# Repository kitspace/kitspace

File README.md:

> ❗ Archived, new development here: [kitspace-v2](https://github.com/kitspace/kitspace-v2)

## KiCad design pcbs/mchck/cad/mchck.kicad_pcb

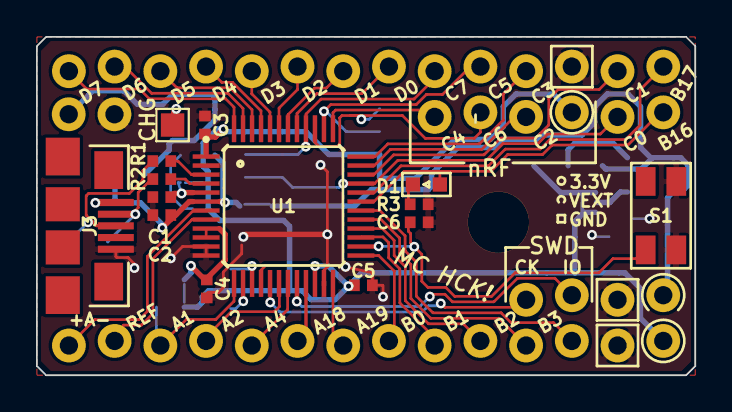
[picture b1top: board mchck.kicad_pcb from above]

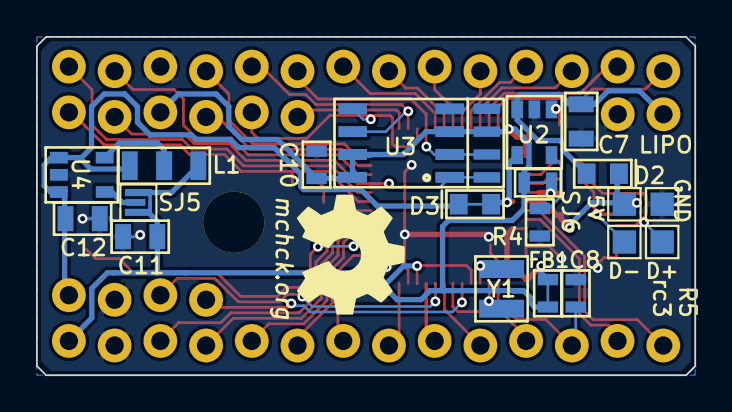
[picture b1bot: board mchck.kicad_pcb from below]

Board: 2 copper layers, 36.6 x 18.8 mm, 41 parts (26 on the bottom side), 51 nets.

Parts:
C1, C2: 2.2u; SMD-1005
C3, C4, C5, C6: 100n; SMD-1005
C7: 4.7u; SM0805
C8, C10: 100n; SM0603_Capa
C11, C12: 10u; SM0805
D1: LED; LED-0603
D2: CDBU0530; SOD-523F
D3: CDBU0530; SOD-523F-NC
FB1: FILTER; SM0603_NC
G1: OHW LOGO; OHW-LOGO-6mm
H1: MOUNTHOLE; mounthole_3mm
J3: MICRO_USB; SparkFun-USB-MICROB
L1: INDUCTOR_SELECT; SM0805-3WAY
P1: RIGHT_PINS; SparkFun-1X06_LOCK
P2: DEBUG; SparkFun-1X04_LOCK
P3: UPPER_PINS; SparkFun-1X14_LOCK
P4: LOWER_PINS; SparkFun-1X14_LOCK
P5: CHG; solderpad
P7: LIPO; SIL100-2
P9: 5V; solderpad
P10: GND; solderpad
P11: D-; solderpad
P12: D+; solderpad
R1, R2: 33; SMD-1005
R3: 1k; SMD-1005
R4: 20k; SM0603
S1: TAC_SWITCHSMD_EVQP2; TACT_4x3
SJ5: SOLDERJUMPERNO; solder-jumper
SJ6: SOLDERJUMPERNC; SM0603_NC
U1: MK20LF; LQFP48
U2: MCP73831-SOT; SOT23-5
U3: SPI_FLASH-X25XXSMD; SparkFun-SO08
U4: MULTIREG; SOT23-5
Y1: CRYSTAL32-SMD; SparkFun-CRYSTAL-32KHZ-SMD

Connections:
/MCU/+5V: C2.1, D2.C, D3.A, J3.1, P9.1, U1.6, U2.4
/MCU/PL1: P4.1, U1.7
/MCU/PL2: P4.2, U1.8
/MCU/PL3: C8.1, P4.3, U1.13
/MCU/PL4: P4.4, U1.18
/MCU/PL5: P4.5, U1.19
/MCU/PL6: P4.6, U1.21
/MCU/PL7: P4.7, U1.24
/MCU/PL8: P4.8, U1.25
/MCU/PL9: P4.9, U1.27
/MCU/PL10: P4.10, U1.28
/MCU/PL11: P4.11, U1.29
/MCU/PL12: P4.12, U1.30
/MCU/PR1: P1.1, U1.37
/MCU/PR2: P1.2, U1.39, U3.5
/MCU/PR3: P1.3, U1.35
/MCU/PR5: P1.5, U1.33, U3.1
/MCU/PR6: D1.1, P1.6, U1.31
/MCU/PU1: P3.1, U1.48
/MCU/PU2: P3.2, U1.47
/MCU/PU3: P3.3, U1.46
/MCU/PU4: P3.4, U1.45
/MCU/PU5: P3.5, U1.44
/MCU/PU6: P3.6, U1.43
/MCU/PU7: P3.7, U1.42
/MCU/PU8: P3.8, U1.41
/MCU/PU9: P3.9, U1.40, U3.2
/MCU/PU10: P3.10, U1.38, U3.6
/MCU/PU11: P3.11, U1.36
/MCU/PU13: P3.13, U1.34
/MCU/PU14: P3.14, U1.32
/MCU/SWD_CLK: P2.1, U1.17
/MCU/SWD_DIO: P2.2, U1.20
/MCU/USB_DM: R2.2, U1.4
/MCU/USB_DP: R1.2, U1.3
/MCU/VREGUSB: C1.1, SJ6.1, U1.5
/USB/USB_D+: J3.3, P12.1, R1.1
/USB/USB_D-: J3.2, P11.1, R2.1
/power/VLIPO: C7.1, D2.A, P7.1, U2.3
/power/VRAW: C12.1, D3.C, L1.1, P2.4, U4.1, U4.3
unnamed: P5.1, U2.1
unnamed: R4.1, U2.5
unnamed: SJ5.2, U4.4
unnamed: L1.2, U4.5
unnamed: U1.14, Y1.X1
unnamed: C6.1, S1.1, U1.26
unnamed: D1.2, R3.1
unnamed: U1.15, Y1.X2
VDD: C3.1, C5.1, C10.1, C11.1, FB1.1, L1.3, P1.4, P4.14, SJ5.1, SJ6.2, U1.1, U1.16, U1.22, U3.3, U3.7, U3.8
VDDA: C4.1, FB1.2, U1.9, U1.10
VSS: C1.2, C2.2, C3.2, C4.2, C5.2, C6.2, C7.2, C8.2, C10.2, C11.2, C12.2, H1.1, J3.5, P2.3, P3.12, P4.13, P7.2, P10.1, R3.2, R4.2, S1.2, S1.4, U1.2, U1.11, U1.12, U1.23, U2.2, U3.4, U4.2

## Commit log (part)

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2021-03-04 Add re-direct for turn signal
2021-03-09 Bump elliptic from 6.5.2 to 6.5.4
    Bumps [elliptic](https://github.com/indutny/elliptic) from 6.5.2 to 6.5.4.
    - [Release notes](https://github.com/indutny/elliptic/releases)
    - [Commits](https://github.com/indutny/elliptic/compare/v6.5.2...v6.5.4)
2021-03-10 Add odour stimulator board (#322)
2021-03-11 Upgrade tracespace tools to ^4.2
2021-03-11 Work around updated whats-that-gerber matching more files
2021-03-12 Make /submit work with updated tracespace
2021-03-12 Add global plausible for custom events
2021-03-12 Add plausible events for extension install
2021-03-12 Omit ibom for maulwurf
2021-03-13 Try aux click handler for aisler
2021-03-15 Remove check for plausible function
2021-03-17 Simplify order PCB tracking
2021-03-17 Add s to Order PCBs event
2021-03-18 Add tinyogx project
2021-03-22 Add openflexure-constant-current-illumination
2021-03-24 Remove smoke test
2021-03-30 Bump y18n from 3.2.1 to 3.2.2
    Bumps [y18n](https://github.com/yargs/y18n) from 3.2.1 to 3.2.2.
    - [Release notes](https://github.com/yargs/y18n/releases)
    - [Changelog](https://github.com/yargs/y18n/blob/master/CHANGELOG.md)
    - [Commits](https://github.com/yargs/y18n/commits)
2021-04-14 Add boards from the beehive project (#329)
2021-04-18 feat: Updates board URL to source repository
    Pull request to merge kitspace code has been merged see https://github.com/drspangle/infidel-sensor/pull/23
2021-04-19 Change beehive url to beehive-org
2021-04-22 Make sure kicad plotting folders for multi are seperate
2021-04-25 Bump ini from 1.3.5 to 1.3.8 (#325)
    Bumps [ini](https://github.com/isaacs/ini) from 1.3.5 to 1.3.8.
    - [Release notes](https://github.com/isaacs/ini/releases)
    - [Commits](https://github.com/isaacs/ini/compare/v1.3.5...v1.3.8)
2021-04-26 Bump http-proxy from 1.18.0 to 1.18.1 (#303)
    Bumps [http-proxy](https://github.com/http-party/node-http-proxy) from 1.18.0 to 1.18.1.
    - [Release notes](https://github.com/http-party/node-http-proxy/releases)
    - [Changelog](https://github.com/http-party/node-http-proxy/blob/master/CHANGELOG.md)
    - [Commits](https://github.com/http-party/node-http-proxy/compare/1.18.0...1.18.1)
2021-05-01 fix: Corrects repo typo
2021-05-05 Added 3 Channel Diversity System Controller (#335)
2021-05-06 Bump ua-parser-js from 0.7.21 to 0.7.28
    Bumps [ua-parser-js](https://github.com/faisalman/ua-parser-js) from 0.7.21 to 0.7.28.
    - [Release notes](https://github.com/faisalman/ua-parser-js/releases)
    - [Commits](https://github.com/faisalman/ua-parser-js/compare/0.7.21...0.7.28)
2021-05-10 Bump hosted-git-info from 2.8.5 to 2.8.9
    Bumps [hosted-git-info](https://github.com/npm/hosted-git-info) from 2.8.5 to 2.8.9.
    - [Release notes](https://github.com/npm/hosted-git-info/releases)
    - [Changelog](https://github.com/npm/hosted-git-info/blob/v2.8.9/CHANGELOG.md)
    - [Commits](https://github.com/npm/hosted-git-info/compare/v2.8.5...v2.8.9)
2021-05-12 Update boards.txt
    Add GPSMux board
2021-05-13 Test Driverino Shield
2021-05-13 Just deploy it
2021-06-10 Run yarn upgrade
2021-06-19 Upgrade netlify-cli, make use of prodIfUnlocked flag
2021-06-19 Add bomanz to omit-ibom
2021-06-20 Work around htmltojsx bug in makeReadme
2021-06-20 Add nasa-jpl/open-source-rover
2021-06-20 Revert "Simplify git cloning process"
    This reverts commit 1f51ce97e80735f7355dbb5525eaeb893e6f500b.
2021-06-20 Try miriam
2021-06-21 Add explicit dep on IBOM.jsx
2021-06-21 Add env vars to github action
2021-06-21 Revert "Stop recording in smoke-test"
    This reverts commit 2b794929cbc1d2cab8aa8b44c51897e9b5f9f131.
2021-06-21 Try basic github action
2021-06-21 Add setup in github action
2021-06-21 Add build step
2021-06-21 Add xvfb to github action
2021-06-21 Try IBOM without X
2021-06-21 Switch InteractiveHtmlBom to kitspace-config-2 branch
2021-06-21 Try using CYPRESS_RECORD_KEY var
2021-06-21 Try deploy using github action
2021-06-21 Remove all travis ci related stuff
2021-06-24 Remove footprints to modules rename for ibom
2021-06-24 Pass on GH_TOKEN to build CI job
2021-06-24 Add Tyler-Ward/stacklight-hardware
2021-06-24 Add gregdavill/d20-hardware
2021-06-25 Add hutscape/oak
2021-06-25 Revert "Add hutscape/oak (#348)"
    This reverts commit 6c3f68caabb1a7c4602ff4b54afc50aa09f63569.
2021-06-25 Try both
2021-06-26 Update 1-click-bom for quantity inference and better tab handling
2021-06-26 Update npm-1-click-bom for better mouser URL parsing
2021-06-28 Add dhairyashah1/USBee32-S2
2021-06-28 Uninstall git lfs before doing get_boards
2021-06-29 Try rigol-DP832-USB-C-adapter
2021-06-30 Try satellite_tracker
2021-07-08 Try hydromisc
2021-07-11 Fix trailing slash on pslab in registry.json
2021-07-11 Try and fix unshallow
2021-07-11 Fix missing && in get_boards
2021-07-12 Work around issue with pslab-hardware shallow clone
2021-07-13 Try parasite
2021-07-14 Update npm-1-click-bom for better header finding
2021-07-15 Update npm-1-click-bom for pcs/pcb alias
2021-07-15 Lock USBee32-S2 to working version
2021-07-16 Try watchy
2021-07-20 Add test_tube_photometer
2021-07-20 Add OtterCastAudioV2
2021-07-20 Add OtterCastAmp (#353)
2021-07-22 Add LibreSolar/mppt-1210-hus
2021-07-23 Add task for remote processing of kicad to layout.svg
2021-07-23 Check for processor failure in makeLayoutSvg.js
2021-08-11 Bump path-parse from 1.0.6 to 1.0.7
    Bumps [path-parse](https://github.com/jbgutierrez/path-parse) from 1.0.6 to 1.0.7.
    - [Release notes](https://github.com/jbgutierrez/path-parse/releases)
    - [Commits](https://github.com/jbgutierrez/path-parse/commits/v1.0.7)
    ---
    updated-dependencies:
    - dependency-name: path-parse
2021-08-20 Remove JLC Assembly columns from BOMs
2021-09-07 Add LouisLab/pivr (#363)
2021-10-07 Correct capitalisation in _redirects
2021-10-08 Add docs about new "pcb-services" field in yaml
2021-10-10 Disable "buy parts" when no parts specified
2021-10-10 Disable "buy parts" when no parts specified (#365)
2021-10-28 Add DropBot test board
2021-11-05 Add DropBot switching board
2021-11-08 Try dropbot 40 channel switching board
2021-11-10 Add dropbot-boards
2021-11-15 Adding ulx4m board
2021-11-16 Bump aws-sdk from 2.658.0 to 2.1030.0
    Bumps [aws-sdk](https://github.com/aws/aws-sdk-js) from 2.658.0 to 2.1030.0.
    - [Release notes](https://github.com/aws/aws-sdk-js/releases)
    - [Changelog](https://github.com/aws/aws-sdk-js/blob/master/CHANGELOG.md)
    - [Commits](https://github.com/aws/aws-sdk-js/compare/v2.658.0...v2.1030.0)
    ---
    updated-dependencies:
2021-11-24 Try Xassette-Asterisk
2021-11-25 Add Xassette-Asterisk (#372)
2021-12-02 Bump jszip from 3.2.2 to 3.7.0
    Bumps [jszip](https://github.com/Stuk/jszip) from 3.2.2 to 3.7.0.
    - [Release notes](https://github.com/Stuk/jszip/releases)
    - [Changelog](https://github.com/Stuk/jszip/blob/master/CHANGES.md)
    - [Commits](https://github.com/Stuk/jszip/compare/v3.2.2...v3.7.0)
    ---
    updated-dependencies:
2022-01-13 Update boards.txt
    add fedwatcher RPi shield
2022-01-13 Add pyphotometry board (#377)
2022-01-19 Temporarily lock-down hoverboard-breakout to working version
2022-02-24 Try air-quality-monitor
2022-02-24 Update kicad to version 6
2022-03-09 Try XboxHDMI
2022-03-10 Fix get_boards
2022-03-15 Bump lodash-es from 4.17.15 to 4.17.21
    Bumps [lodash-es](https://github.com/lodash/lodash) from 4.17.15 to 4.17.21.
    - [Release notes](https://github.com/lodash/lodash/releases)
    - [Commits](https://github.com/lodash/lodash/compare/4.17.15...4.17.21)
    ---
    updated-dependencies:
    - dependency-name: lodash-es
2022-04-01 Temporarily lock down OtterCastV2 to working version
2022-05-16 Bump nanoid from 3.1.23 to 3.3.4
    Bumps [nanoid](https://github.com/ai/nanoid) from 3.1.23 to 3.3.4.
    - [Release notes](https://github.com/ai/nanoid/releases)
    - [Changelog](https://github.com/ai/nanoid/blob/main/CHANGELOG.md)
    - [Commits](https://github.com/ai/nanoid/compare/3.1.23...3.3.4)
    ---
    updated-dependencies:
2022-06-23 Bump jsdom from 9.12.0 to 16.5.0
    Bumps [jsdom](https://github.com/jsdom/jsdom) from 9.12.0 to 16.5.0.
    - [Release notes](https://github.com/jsdom/jsdom/releases)
    - [Changelog](https://github.com/jsdom/jsdom/blob/master/Changelog.md)
    - [Commits](https://github.com/jsdom/jsdom/compare/9.12.0...16.5.0)
    ---
    updated-dependencies:
2022-06-23 Update jsdom to 20
2022-06-28 Adding balthazar-space keyboard (#387)
2022-06-29 One more board from balthazar-space (#388)
2022-06-29 Upgrade to kicad 6
2022-06-29 Hack for ibom config
2022-06-29 Revert "One more board from balthazar-space (#388)"
    This reverts commit f111a90ce9a32853e59d0c420332aa9e1a4c1be6.
2022-06-29 Adding Unifying board (#389)
2022-07-03 Add Open-Gamma-Detector (#391)
2022-07-08 Bump moment from 2.27.0 to 2.29.4
    Bumps [moment](https://github.com/moment/moment) from 2.27.0 to 2.29.4.
    - [Release notes](https://github.com/moment/moment/releases)
    - [Changelog](https://github.com/moment/moment/blob/develop/CHANGELOG.md)
    - [Commits](https://github.com/moment/moment/compare/2.27.0...2.29.4)
    ---
    updated-dependencies:
2022-07-13 Remove test
2022-07-14 Add key-ripper
    https://github.com/bschwind/key-ripper/pull/13
2022-07-15 Try 4chord-midi
2022-07-20 Fix isssue with finding .kicad_pcb
2022-07-28 Add threeboard
    https://github.com/taylorconor/threeboard/pull/9
2022-09-20 Try micro-bot on its own
2022-09-20 Update boards.txt
    Added four Rosmo.io boards
2022-09-28 Revert "Temporarily remove diplexer"
    This reverts commit 248b8678cd7bbb9ea7cfa7f704172fa42ca547c5.
2022-09-30 Update _redirects
2022-10-01 Temporarily remove piezo-sensor
2022-10-02 Add diplexer and 8bitmixtape to omit ibom
2022-10-02 Try default kicad on ubuntu 22.04
2022-10-02 Revert "Temporarily remove piezo-sensor"
    This reverts commit 31f23a8333b428d7a1ec631651fee4355b889e40.
2022-10-03 Try updated nunchuk
2022-10-05 Add spikeling v2.0 (#400)
2022-11-15 [ImgBot] Optimize images
    *Total -- 413.61kb -> 322.15kb (22.11%)
    /image_src/submit.svg -- 2.60kb -> 0.94kb (64.05%)
    /docs/planned.png -- 41.96kb -> 15.79kb (62.37%)
    /docs/current.png -- 26.25kb -> 11.59kb (55.84%)
    /src/images/logo.png -- 12.94kb -> 6.34kb (51%)
    /src/images/mag_icon.svg -- 3.06kb -> 1.50kb (50.78%)
2022-11-16 Increase outline gap fill to 9mm
2022-12-01 Add redirect for BeeHive/boards
2022-12-02 add rrf_rpi_skr_adapter (#401)
2022-12-04 Add ArdPromSD (#405)
2023-01-06 Bump json5 from 2.1.3 to 2.2.3
    Bumps [json5](https://github.com/json5/json5) from 2.1.3 to 2.2.3.
    - [Release notes](https://github.com/json5/json5/releases)
    - [Changelog](https://github.com/json5/json5/blob/main/CHANGELOG.md)
    - [Commits](https://github.com/json5/json5/compare/v2.1.3...v2.2.3)
    ---
    updated-dependencies:
2023-01-09 Update breakpoint for more pcb services
2023-01-16 Add redirects for OpenGammaProject rename
2023-01-16 Try breadboard-io
2023-01-16 Update npm-1-click-bom
2023-01-23 Bump cookiejar from 2.1.2 to 2.1.4
    Bumps [cookiejar](https://github.com/bmeck/node-cookiejar) from 2.1.2 to 2.1.4.
    - [Release notes](https://github.com/bmeck/node-cookiejar/releases)
    - [Commits](https://github.com/bmeck/node-cookiejar/commits)
    ---
    updated-dependencies:
    - dependency-name: cookiejar
2023-01-31 Lock down key-ripper
2023-01-31 Re-direct key-ripper to multi project
2023-02-01 Use repoPath for readme pattern
2023-02-02 Bump jszip from 3.2.2 to 3.8.0
    Bumps [jszip](https://github.com/Stuk/jszip) from 3.2.2 to 3.8.0.
    - [Release notes](https://github.com/Stuk/jszip/releases)
    - [Changelog](https://github.com/Stuk/jszip/blob/main/CHANGES.md)
    - [Commits](https://github.com/Stuk/jszip/compare/v3.2.2...v3.8.0)
    ---
    updated-dependencies:
2023-02-11 Revert "Temp change add-a-project link to readme"
    This reverts commit 163f92471d41c21dfbb9c52c33510b4cfa23ff2c.
2023-02-11 Remove links to /submit
2023-02-14 Try mlab USBI2C01
2023-02-15 Adding MLAB USBI2C01 (#413)
2023-02-19 Test node version
2023-02-19 Try kicad 7
2023-04-06 Disable running github action on cron schedule
2023-04-15 Lock down ruler to kicad 6 version
2023-04-15 Add MicroFC-SiPM-Array-Board (#414)
2023-05-17 Add favicons in many more sizes
2023-05-30 Add more favicons
2023-06-13 Add Tiny-MicroFC-Carrier-Board (#415)
2023-11-12 Revert "Allow triggering via workflow dispatch"
    This reverts commit 6cec54e4d87b6ea541cc9c68905a9ef7b44c00d8.
2024-04-27 Add hawk (#417)

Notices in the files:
pcbs/mchck/cad/mchck.kicad_pcb:
(c) 2011,2012,2013 Simon Schubert
CERN OHL v.1.1 or later
